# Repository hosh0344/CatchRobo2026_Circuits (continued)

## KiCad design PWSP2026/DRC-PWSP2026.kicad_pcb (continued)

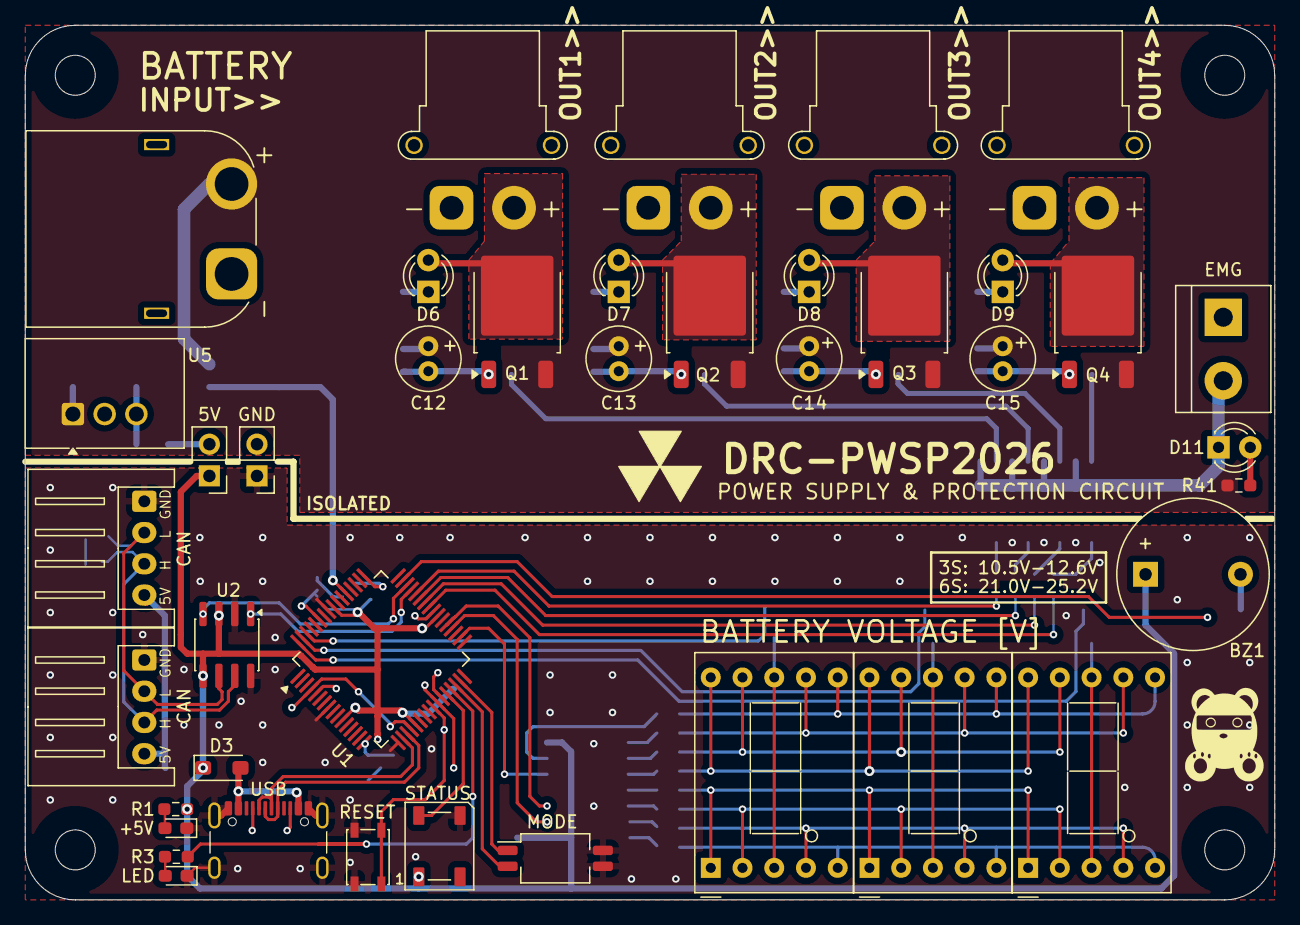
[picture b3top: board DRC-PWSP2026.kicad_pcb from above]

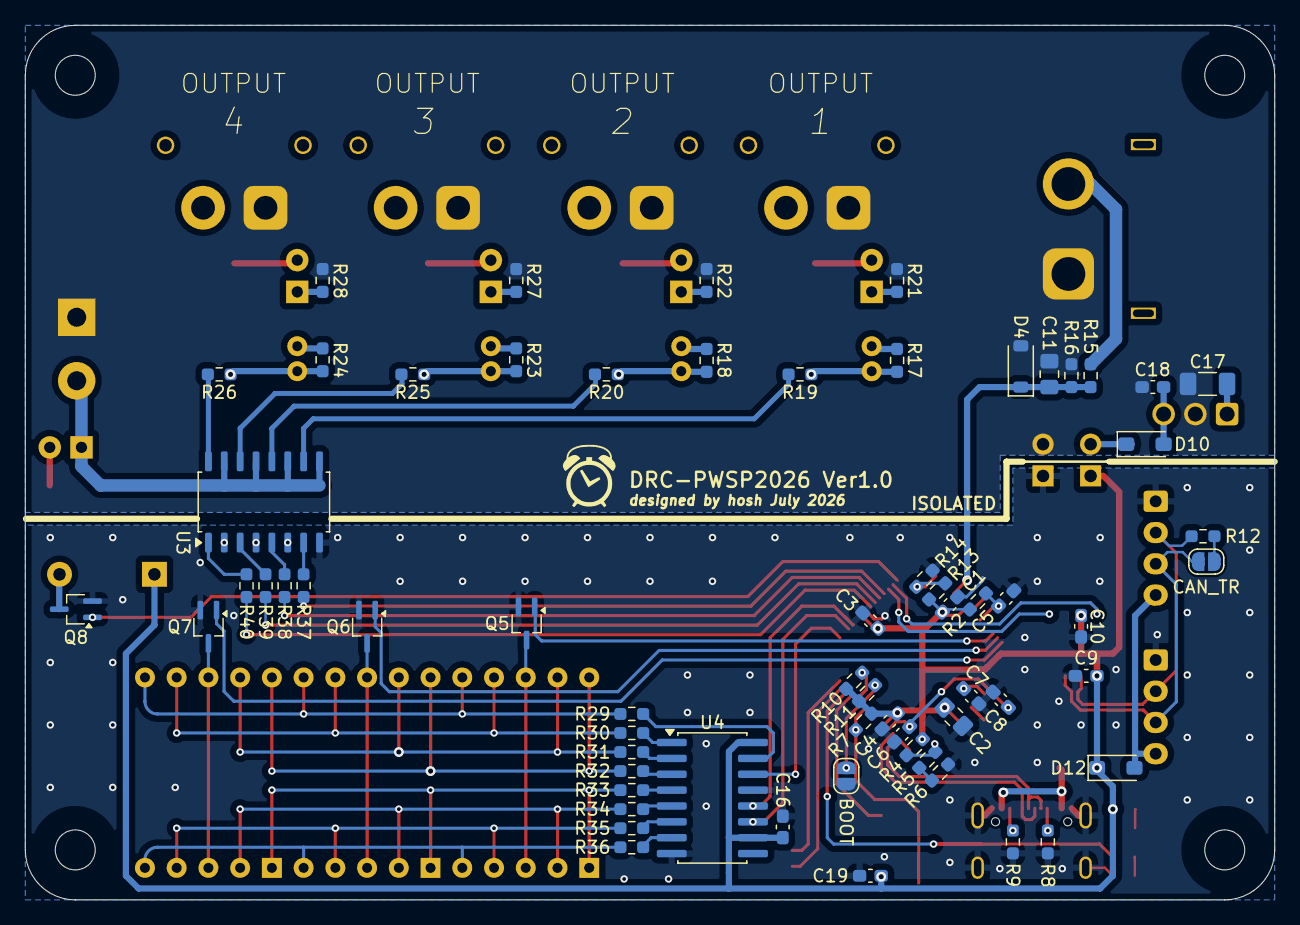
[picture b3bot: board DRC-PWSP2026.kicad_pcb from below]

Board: 2 copper layers, 100.0 x 70.0 mm, 104 parts (64 on the bottom side), 86 nets.

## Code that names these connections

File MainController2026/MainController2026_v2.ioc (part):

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Mcu.Name=STM32G474R(B-C-E)Tx
Mcu.Package=LQFP64
Mcu.UserName=STM32G474RETx
PA0.Mode=IN1-Single-Ended
PA0.Signal=ADC1_IN1
PA1.Mode=IN2-Single-Ended
PA1.Signal=ADC1_IN2
PA10.GPIOParameters=GPIO_Label
PA10.GPIO_Label=RES
PA10.Signal=GPIO_Output
PA13.Mode=Serial_Wire
PA13.Signal=SYS_JTMS-SWDIO
PA14.Mode=Serial_Wire
PA14.Signal=SYS_JTCK-SWCLK
PA2.Mode=IN3-Single-Ended
PA2.Signal=ADC1_IN3
PA3.Mode=IN4-Single-Ended
PA3.Signal=ADC1_IN4
PA4.GPIOParameters=GPIO_Label
PA4.GPIO_Label=JOY_L
PA4.Signal=GPIO_Input
PA5.Mode=TX_Only_Simplex_Unidirect_Master
PA5.Signal=SPI1_SCK
PA6.GPIOParameters=GPIO_Label
PA6.GPIO_Label=DC
PA6.Signal=GPIO_Output
PA7.Mode=TX_Only_Simplex_Unidirect_Master
PA7.Signal=SPI1_MOSI
PA9.GPIOParameters=GPIO_Label
PA9.GPIO_Label=CS
PA9.Signal=GPIO_Output
PB0.GPIOParameters=GPIO_Label
PB0.GPIO_Label=RIGHT_R
PB0.Signal=GPIO_Input
PB1.GPIOParameters=GPIO_Label
PB1.GPIO_Label=UP_R
PB1.Signal=GPIO_Input
PB10.GPIOParameters=GPIO_Label
PB10.GPIO_Label=DOWN_R
PB10.Signal=GPIO_Input
PB12.Mode=FDCAN_Activate
PB12.Signal=FDCAN2_RX
PB13.Mode=FDCAN_Activate
PB13.Signal=FDCAN2_TX
PB14.GPIOParameters=GPIO_Label
PB14.GPIO_Label=SIDE_R
PB14.Signal=GPIO_Input
PB15.GPIOParameters=GPIO_Label
PB15.GPIO_Label=SIDE_ZR
PB15.Signal=GPIO_Input
PB2.GPIOParameters=GPIO_Label
PB2.GPIO_Label=LEFT_R
PB2.Signal=GPIO_Input
PB3.GPIOParameters=GPIO_Label
PB3.GPIO_Label=SIDE_L
PB3.Signal=GPIO_Input
PB4.GPIOParameters=GPIO_Label
PB4.GPIO_Label=SIDE_ZL
PB4.Signal=GPIO_Input
PC0.GPIOParameters=GPIO_Label
PC0.GPIO_Label=DOWN_L
PC0.Signal=GPIO_Input
PC1.GPIOParameters=GPIO_Label
PC1.GPIO_Label=RIGHT_L
PC1.Signal=GPIO_Input
PC14-OSC32_IN.GPIOParameters=GPIO_Label
PC14-OSC32_IN.GPIO_Label=JOY_R
PC14-OSC32_IN.Signal=GPIO_Input
PC2.GPIOParameters=GPIO_Label
PC2.GPIO_Label=UP_L
PC2.Signal=GPIO_Input
PC3.GPIOParameters=GPIO_Label
PC3.GPIO_Label=LEFT_L
PC3.Signal=GPIO_Input
PC4.Mode=Asynchronous
PC4.Signal=USART1_TX
PC5.Mode=Asynchronous
PC5.Signal=USART1_RX
PC6.Signal=S_TIM8_CH1
PC7.Signal=S_TIM8_CH2
PC8.Signal=S_TIM8_CH3
PC9.GPIOParameters=GPIO_Label
PC9.GPIO_Label=BLK
PC9.Signal=GPIO_Output
PF0-OSC_IN.Mode=HSE-External-Oscillator
PF0-OSC_IN.Signal=RCC_OSC_IN
PF1-OSC_OUT.Mode=HSE-External-Oscillator
PF1-OSC_OUT.Signal=RCC_OSC_OUT
RCC.HSE_VALUE=16000000
RCC.SYSCLKFreq_VALUE=160000000
RCC.SYSCLKSource=RCC_SYSCLKSOURCE_PLLCLK
board=custom

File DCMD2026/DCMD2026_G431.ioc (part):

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Mcu.Name=STM32G431C(6-8-B)Tx
Mcu.Package=LQFP48
Mcu.UserName=STM32G431CBTx
PA1.Signal=S_TIM2_CH2
PA11.Mode=FDCAN_Activate
PA11.Signal=FDCAN1_RX
PA12.Mode=FDCAN_Activate
PA12.Signal=FDCAN1_TX
PA13.Mode=Serial_Wire
PA13.Signal=SYS_JTMS-SWDIO
PA14.Mode=Serial_Wire
PA14.Signal=SYS_JTCK-SWCLK
PA15.Mode=Asynchronous
PA15.Signal=USART2_RX
PA2.Signal=S_TIM2_CH3
PA3.Signal=S_TIM2_CH4
PA5.GPIOParameters=GPIO_Label
PA5.GPIO_Label=ENC_X
PA5.Signal=GPIO_Input
PA6.Signal=S_TIM3_CH1
PA7.Signal=S_TIM3_CH2
PA8.Signal=S_TIM1_CH1
PA9.Signal=S_TIM1_CH2
PB0.GPIOParameters=GPIO_Label
PB0.GPIO_Label=LIM
PB0.Signal=GPIO_Input
PB3.Mode=Asynchronous
PB3.Signal=USART2_TX
PB4.GPIOParameters=GPIO_Label
PB4.GPIO_Label=LED
PB4.Signal=GPIO_Output
PF0-OSC_IN.Mode=HSE-External-Oscillator
PF0-OSC_IN.Signal=RCC_OSC_IN
PF1-OSC_OUT.Mode=HSE-External-Oscillator
PF1-OSC_OUT.Signal=RCC_OSC_OUT
RCC.HSE_VALUE=16000000
RCC.SYSCLKFreq_VALUE=160000000
RCC.SYSCLKSource=RCC_SYSCLKSOURCE_PLLCLK
board=custom

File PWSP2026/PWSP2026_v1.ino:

//#include <Arduino_CAN.h>
#include <Adafruit_NeoPixel.h>
//CAN通信
#define CAN_RX 5
#define CAN_TX 4

//7セグメントLED
#define DIGI0 A3
#define DIGI1 A2
#define DIGI2 A1
#define CS 10
#define SER 11
#define SCK 13

//電圧測定用
#define VSENS A0

//ステータスLED
#define RGB 8

//ブザー
#define BZ A4
#define BZ_Frequency 500

//DIPスイッチ
#define ID0 0
#define ID1 1

//電源分配出力
#define SW1 3
#define SW2 2
#define SW3 6
#define SW4 7

int control_period= 1000; // 制御周期

//各基準電圧
const float V_ref = 4.67;  // ADCの基準電圧 (USBで電源供給時は5V, LiPo経由だと4.7Vくらい)
const float V_max = 10;
const float V_min = 1;

//ブザー用フラグ
bool buzzer_on;
uint32_t buzzer_start = 0;
bool low_voltage_alarm = false;

const int melody[] = {2000, 1300};
const int duration[] = {120, 180};

Adafruit_NeoPixel pixels(1, RGB, NEO_GRB + NEO_KHZ800);

uint8_t digit_pattern[16] = {
  B11101110,  // 0
  B10000010,  // 1
  B11011100,  // 2
  B11010110,  // 3
  B10110010,  // 4
  B01110110,  // 5
  B01111110,  // 6
  B11000010,  // 7
  B11111110,  // 8
  B11110110,  // 9
};

uint8_t emoji_pattern[][3] = {
  // 真顔
  {
    B11110000,
    B00000100,
    B11110000,
  },
  // お目々閉じ
  {
    B00010000,
    B00000100,
    B00010000,
  },
  // ニコッ
  {
    B11110000,
    B00001110,
    B11110000,
  },
};

void setup() {
  Serial.begin(115200);  //シリアル初期化
  analogReadResolution(10); //ADCの分解能を10bitに設定(最大14bit)

  //LEDピン設定
  pinMode(DIGI0, OUTPUT);
  pinMode(DIGI1, OUTPUT);
  pinMode(DIGI2, OUTPUT);
  pinMode(BZ, OUTPUT);
  pinMode(CS, OUTPUT);
  pinMode(SER, OUTPUT);
  pinMode(SCK, OUTPUT);
  pinMode(VSENS, INPUT);

  //出力ピン設定
  pinMode(SW1, OUTPUT);
  pinMode(SW2, OUTPUT);
  pinMode(SW3, OUTPUT);
  pinMode(SW4, OUTPUT);
  pinMode(RGB, OUTPUT);

  digitalWrite(CS, HIGH);


  // 顔を表示
  /*display_pattern_for_duration(emoji_pattern[0], 1000);
  display_pattern_for_duration(emoji_pattern[1], 100);
  display_pattern_for_duration(emoji_pattern[0], 200);
  display_pattern_for_duration(emoji_pattern[1], 100);
  display_pattern_for_duration(emoji_pattern[0], 2000);
  display_pattern_for_duration(emoji_pattern[2], 1500);*/
  
  //ステータスLEDを点灯(通常時は青)
  pixels.begin();
  pixels.setBrightness(64);  //輝度(0～255)
  pixels.setPixelColor(0, pixels.Color(0, 255, 255));  //LEDの色
  pixels.show();

  StartSound();

  //電源分配開始
  digitalWrite(SW1, HIGH);
  digitalWrite(SW2, HIGH);
  digitalWrite(SW3, HIGH);
  digitalWrite(SW4, HIGH);

}


void loop() {
  static float voltage = 0;

  static long unsigned int rx_id;
  static unsigned char len;
  static unsigned char rx_buf[8];

  static uint32_t last_voltage_check = millis();
  if (millis() - last_voltage_check > control_period) {
    last_voltage_check = millis();
    voltage = get_voltage();
    Serial.println(voltage);  //デバッグ用

    // 電圧が1-10V未満ならブザーを鳴らす
   if (voltage < V_max && voltage > V_min) {
      if (!low_voltage_alarm) {
      //tone(BZ, BZ_Frequency);
      buzzer_start = millis();
      buzzer_on = true;
      low_voltage_alarm = true;

      pixels.setPixelColor(0, pixels.Color(255, 0, 0));
      pixels.show();
    }
      if (buzzer_on && millis() - buzzer_start >= 3000) {
        noTone(BZ);
        buzzer_on = false;
    }
  }
      else {
      noTone(BZ);
      low_voltage_alarm = false;
      pixels.setPixelColor(0, pixels.Color(0, 255, 255));
      pixels.show();
    }
  }

  //電圧の表示
  uint32_t v = (uint32_t)(voltage * 10);  // 例: 12.3V → 123
  uint8_t tens = (v / 100) % 10;          // 十の位
  uint8_t ones = (v / 10) % 10;           // 一の位
  uint8_t deci = v % 10;                  // 小数第一位
  const uint8_t voltage_digits[3] = {
    digit_pattern[tens],
    digit_pattern[ones] | B00000001,  //小数点表示
    digit_pattern[deci],
  };
  display_pattern(voltage_digits);

}

//電圧フィードバック
float get_voltage() {
  float voltage = analogRead(VSENS) * (V_ref / 1023.0) * ((10.0 + 2.2) / 2.2); 
  return voltage;
}

//7セグの表示
void display_pattern(const uint8_t pattern[3]) {
  digitalWrite(DIGI0, LOW);
  digitalWrite(DIGI1, LOW);
  digitalWrite(DIGI2, LOW);
  digitalWrite(CS, LOW);
  shiftOut(SER, SCK, LSBFIRST, pattern[0]);
  digitalWrite(CS, HIGH);
  digitalWrite(DIGI0, HIGH);
  digitalWrite(DIGI1, LOW);
  digitalWrite(DIGI2, LOW);
  delay(1);
  digitalWrite(DIGI0, LOW);
  digitalWrite(DIGI1, LOW);
  digitalWrite(DIGI2, LOW);
  digitalWrite(CS, LOW);
  shiftOut(SER, SCK, LSBFIRST, pattern[1]);
  digitalWrite(CS, HIGH);
  digitalWrite(DIGI0, LOW);
  digitalWrite(DIGI1, HIGH);
  digitalWrite(DIGI2, LOW);
  delay(1);
  digitalWrite(DIGI0, LOW);
  digitalWrite(DIGI1, LOW);
  digitalWrite(DIGI2, LOW);
  digitalWrite(CS, LOW);
  shiftOut(SER, SCK, LSBFIRST, pattern[2]);
  digitalWrite(CS, HIGH);
  digitalWrite(DIGI0, LOW);
  digitalWrite(DIGI1, LOW);
  digitalWrite(DIGI2, HIGH);
  delay(1);
}

//7セグの表示(時間指定)
void display_pattern_for_duration(const uint8_t pattern[3], const uint32_t duration) {
  uint32_t start = millis();
  while (true) {
    display_pattern(pattern);
    if (millis() - start > duration) {
      break;
    }
  }
}

void StartSound() {
  for (int i = 0; i < 2; i++) {
    tone(BZ, melody[i]);
    delay(duration[i]);
  }
  noTone(BZ);
}
